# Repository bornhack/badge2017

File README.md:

# Bornhack Badge 2017

## About the hardware

The Bornhack 2017 badge is based around a SiLabs Happy Gecko microcontroller,
an OLED graphical display, a few buttons and a USB interface.

The microcontroller is a Cortex-M0+ with built in USB, specifically we are using
the EFM32HG322F64G and one of the 128x64 pixels OLED displays with an SSD1306
controller.

We have separated the hardware design files from the code and put them in the
[hardware branch][hardware] for you to have a look at and build on.

You can download the microcontroller [reference manual][manual] and
[datasheet][] directly from [SiliconLabs][silabs].

[hardware]: https://github.com/bornhack/badge2017/tree/hardware
[silabs]: https://www.silabs.com/
[manual]: https://www.silabs.com/documents/public/reference-manuals/EFM32HG-RM.pdf
[datasheet]: https://www.silabs.com/documents/public/data-sheets/EFM32HG322.pdf

## About the code

This repo is meant as a starting point for developing your own code
for the Bornhack 2017 badge.

Although *main.c* is quite long it is not meant to scare you. Rather it is
meant to show in all its gory details how to actually program microcontrollers
that doesn't run any operating system without hiding anything behind
a thick API. However to make things readable it does make use of the
[geckonator][] library. This is a very thin wrapper around the registers
of the Happy Gecko chip on the badge. It allows us to write something like
```c
clock_rtc_disable();
```
rather than the more cryptic
```c
CMU->LFACLKEN0 &= ~CMU_LFACLKEN0_RTC;
```
Don't worry. The compiler will sort it out and do exactly as if you'd written the
cryptic version.

Scroll to the bottom of *main.c* and you'll see an infinite loop.
This is the 'mainloop' of the program. It simply waits for events
such as button presses and reacts to those. When there are no
more events to be processed in the internal queue you'll get one last `EVENT_LAST`
event before the chip will sleep and wait for more events.

Events are added to the queue by the interrupt handler functions. You can recognize those
by the fact that they're public (ie. not marked by `static`) and their name will
end in `_IRQHandler`. Before entering the mainloop the chip is configured to
call these handlers on certain events such the voltage on a pin dropping from above 1.5V
to below 0.3V caused by the press of a button.

[geckonator]: https://github.com/flummer/geckonator

## Develop software online

Go to [badge.xil.se](https://badge.xil.se/), click "All Projects" and choose
the official example. Start hacking. Once your code compiles this is how you program
your badge:

1. Click the "Download binary" button to download the compiled code.
2. Connect the USB cable to the board and your computer.
3. Press the **BOOT** button on the badge.
4. Copy the downloaded `.bin`-file to the `GECKOBOOT` USB stick that appeared on your computer.
5. Eject (or unmount) the USB stick, and watch your code run.

## Develop software locally

### 1. Install dependencies

##### Archlinux
```sh
pacman -S arm-none-eabi-gcc arm-none-eabi-newlib make
```

##### Debian/Ubuntu
```sh
apt-get install gcc-arm-none-eabi libnewlib-arm-none-eabi make
```
Unfortunately the toolchain in Ubuntu Trusty 14.04 is too old to work out of the box.

##### Fedora
```sh
dnf install arm-none-eabi-gcc arm-none-eabi-newlib make
```

##### OSX

Download an arm-none-eabi toolchain from ARM [here][arm-toolchain].
Unpack the tarball and update your PATH variable to point to the unpacked `bin` directory.

##### Windows
###### Option 1
Download the apropriate installer from ARM [here][arm-toolchain].
Install it and update your path.
You'll also need GNU Make installed.
A pre-built version can be downloaded [here](http://gnuwin32.sourceforge.net/packages/make.htm).

###### Option 2

Use Windows Subsystem for Linux with Ubuntu 16.04 Xenial or newer and proceed as on Ubuntu above.

### 2. Get the source code

If you already have git installed
```
git clone https://github.com/bornhack/badge2017.git
cd badge2017
```

Otherwise you can download a tarball or zip file from
[https://github.com/bornhack/badge2017](https://github.com/bornhack/badge2017)

### 3. Build the code
Simply type `make` in the downloaded directory.
If the build fails (fx. on Debian Jessie and Ubuntu Xenial)
try editing the `Makefile` and uncommenting the line which says `OLD=1`.

If there are no compilation errors this will result in a `code.bin` in the `out` directory.

[arm-toolchain]: https://developer.arm.com/open-source/gnu-toolchain/gnu-rm/downloads

### 4. Program the badge with your compiled code

###### Option 1

Proceed as above, but instead of downloading your `.bin`-file use the `out/code.bin` you
just generated above.

###### Option 2

Alternatively you can install a program called *dfu-util*. With this program installed
you can simply put the badge in bootloader mode by pressing the **BOOT** button,
and then type `make dfu`. Usually your dfu-util package comes with rules to give
your user (and hence dfu-util) access to the raw USB device. If not you might need
`sudo make dfu`.

## Examples developed during Bornhack 2017

This repo also contains a few branches with examples developed at Barnhack. You can check them out locally with
```sh
git clone -b <BRANCH> https://github.com/bornhack/badge2017.git
```
..or just switch to the branch in your regular clone of this repo.

- [gimp](https://github.com/bornhack/badge2017/tree/gimp) - [gimp](https://www.gimp.org/) can export pictures as C-code usable on the badge
- [bornhackfish](https://github.com/bornhack/badge2017/tree/bornhackfish) - Standard example, but with fish and physics
- [snake](https://github.com/bornhack/badge2017/tree/snake) - Play snake on your badge
- [starfield](https://github.com/bornhack/badge2017/tree/starfield) - Fly through space

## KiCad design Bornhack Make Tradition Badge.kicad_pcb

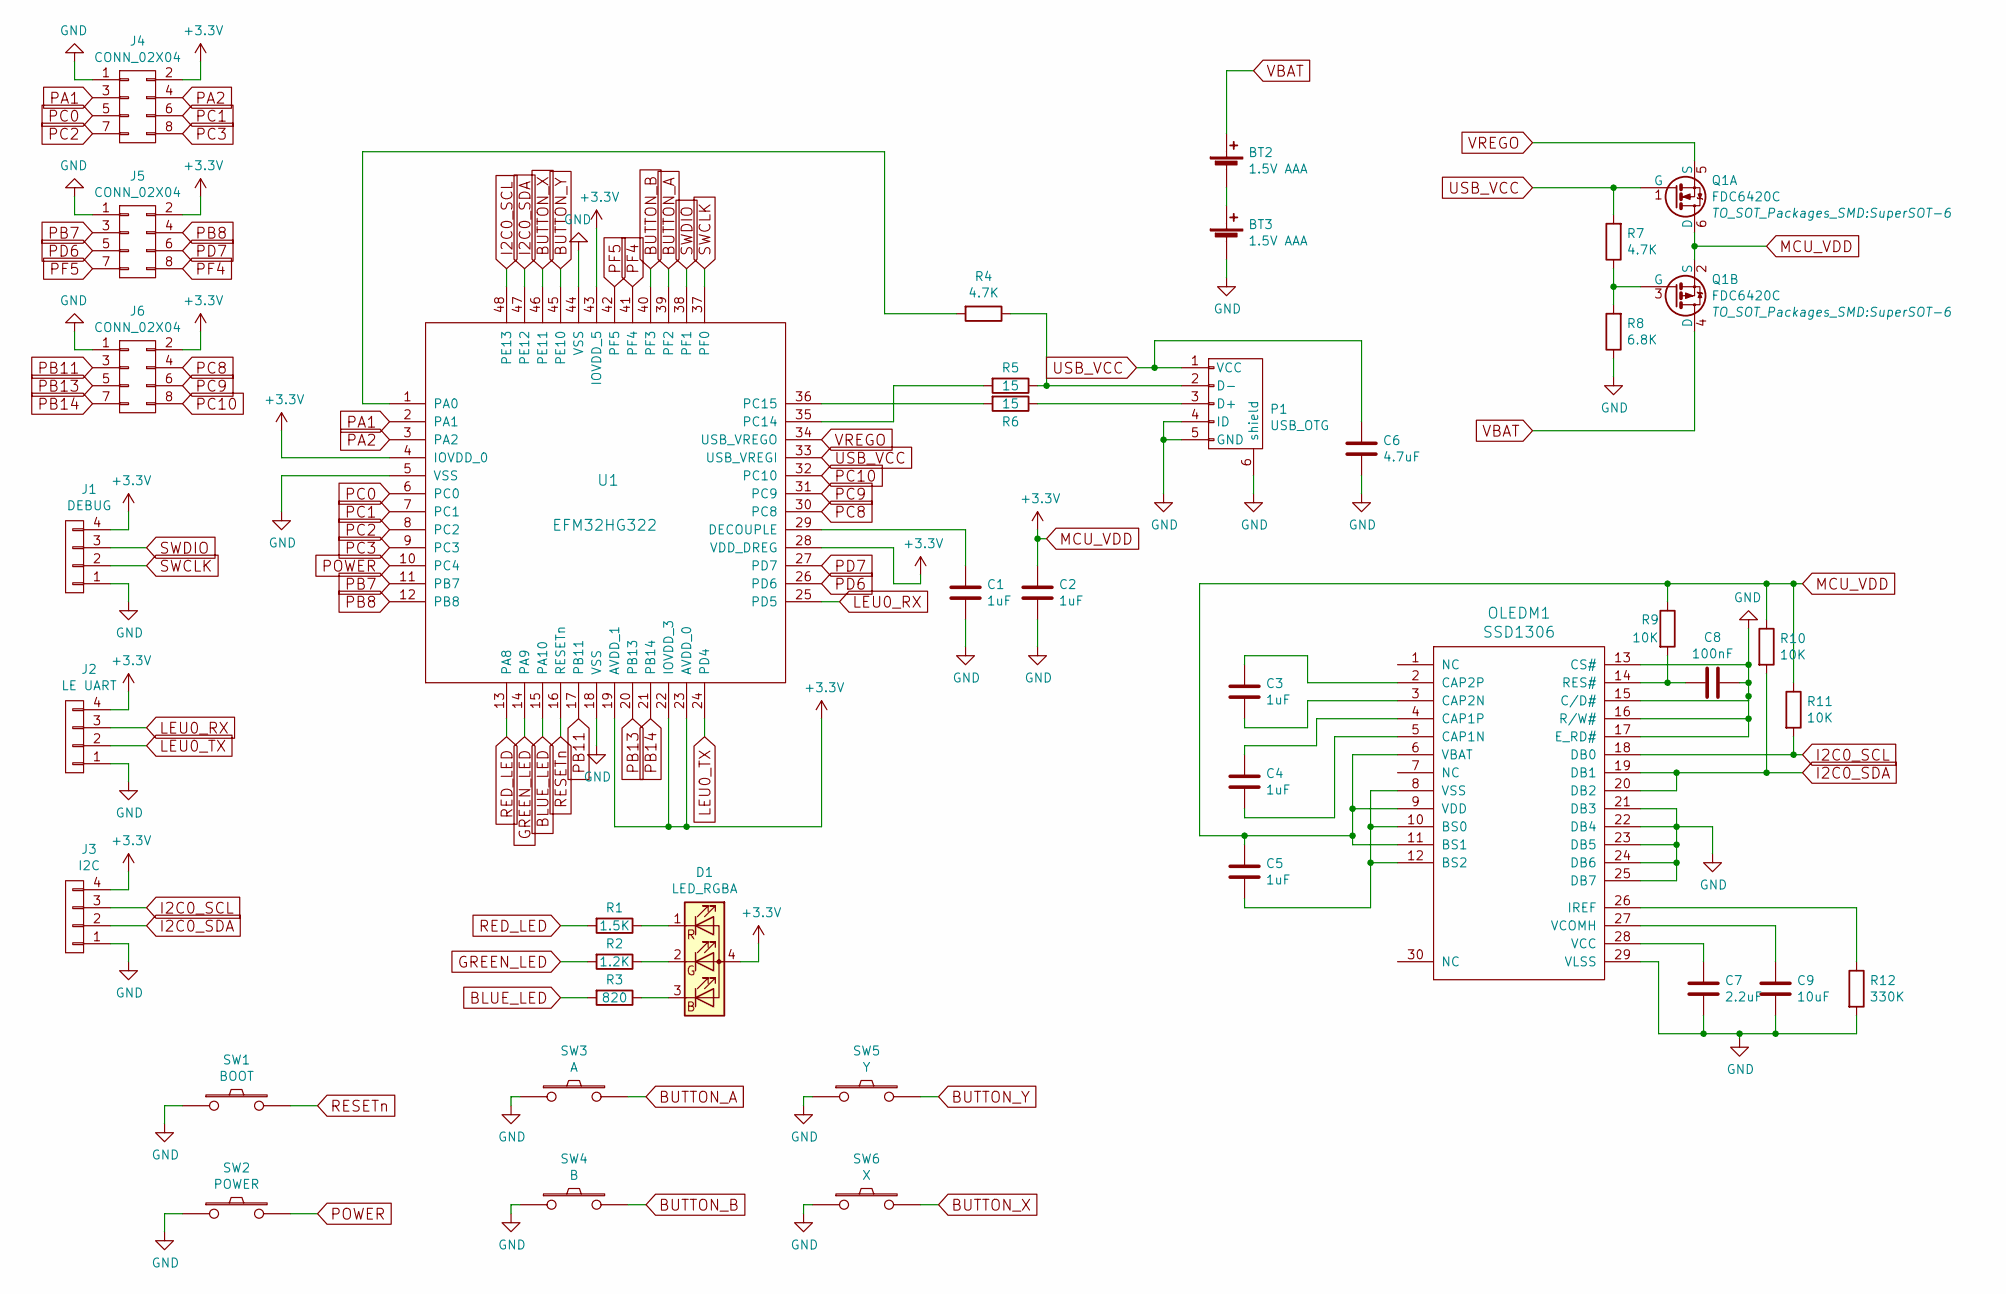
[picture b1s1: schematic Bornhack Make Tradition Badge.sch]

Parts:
BT2, BT3: 1.5V AAA; Keystone_555_AAA_Battery_Clip_pair
C1, C2, C3, C4, C5: 1uF; C_0805
C6: 4.7uF; C_0805
C7: 2.2uF; C_0805
C8: 100nF; C_0805
C9: 10uF; C_0805
D1: LED_RGBA; RGBA_LED_SMD_0606
J1: DEBUG; Pin_Header_Straight_1x04_Pitch2.54mm
J2: LE UART; Pin_Header_Straight_1x04_Pitch2.54mm
J3: I2C; Pin_Header_Straight_1x04_Pitch2.54mm
J4, J5, J6: CONN_02X04; Pin_Header_Straight_2x04_Pitch2.54mm
OLEDM1: SSD1306; IROP055-SSD1306Z
P1: USB_OTG; USB_Micro-B_10103594-0001LF
Q1: FDC6420C; SuperSOT-6
R1: 1.5K; R_0805
R2: 1.2K; R_0805
R3: 820; R_0805
R4, R7: 4.7K; R_0805
R5, R6: 15; R_0805
R8: 6.8K; R_0805
R9, R10, R11: 10K; R_0805
R12: 330K; R_0805
SW1: BOOT; SW_SPST_PTS645
SW2: POWER; SW_SPST_PTS645
SW3: A; SW_SPST_PTS645
SW4: B; SW_SPST_PTS645
SW5: Y; SW_SPST_PTS645
SW6: X; SW_SPST_PTS645
U1: EFM32HG322; TQFP-48_7x7mm_Pitch0.5mm

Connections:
BLUE_LED: R3.2, U1.15 (PA10)
BUTTON_A: SW3.2, U1.39 (PF2)
BUTTON_B: SW4.2, U1.40 (PF3)
BUTTON_X: SW6.2, U1.46 (PE11)
BUTTON_Y: SW5.2, U1.45 (PE10)
GND: BT3.2 (-), C1.2, C2.2, C6.2, C7.2, C8.1, C9.2, J1.1, J2.1, J3.1, J4.1, J5.1, J6.1, OLEDM1.13 (CS#), OLEDM1.15 (C/D#), OLEDM1.16 (R/W#), OLEDM1.17 (E_RD#), OLEDM1.21 (DB3), OLEDM1.22 (DB4), OLEDM1.23 (DB5), OLEDM1.24 (DB6), OLEDM1.25 (DB7), OLEDM1.29 (VLSS), P1.4 (ID), P1.5 (GND), P1.6 (shield), R8.1, R12.2, SW1.1, SW2.1, SW3.1, SW4.1, SW5.1, SW6.1, U1.5 (VSS), U1.18 (VSS), U1.44 (VSS)
GREEN_LED: R2.2, U1.14 (PA9)
I2C0_SCL: J3.3, OLEDM1.18 (DB0), R11.2, U1.48 (PE13)
I2C0_SDA: J3.2, OLEDM1.19 (DB1), OLEDM1.20 (DB2), R10.2, U1.47 (PE12)
LEU0_RX: J2.3, U1.25 (PD5)
LEU0_TX: J2.2, U1.24 (PD4)
MCU_VDD: C2.1, C5.1, D1.4 (A), J1.4, J2.4, J3.4, J4.2, J5.2, J6.2, OLEDM1.6 (VBAT), OLEDM1.9 (VDD), OLEDM1.11 (BS1), Q1.2 (S), Q1.6 (D), R9.1, R10.1, R11.1, U1.4 (IOVDD_0), U1.19 (AVDD_1), U1.22 (IOVDD_3), U1.23 (AVDD_0), U1.28 (VDD_DREG), U1.43 (IOVDD_5)
unnamed: BT2.2 (-), BT3.1 (+)
unnamed: C1.1, U1.29 (DECOUPLE)
unnamed: C3.1, OLEDM1.2 (CAP2P)
unnamed: C3.2, OLEDM1.3 (CAP2N)
unnamed: C4.1, OLEDM1.4 (CAP1P)
unnamed: C4.2, OLEDM1.5 (CAP1N)
unnamed: C5.2, OLEDM1.8 (VSS), OLEDM1.10 (BS0), OLEDM1.12 (BS2)
unnamed: C7.1, OLEDM1.28 (VCC)
unnamed: C8.2, OLEDM1.14 (RES#), R9.2
unnamed: C9.1, OLEDM1.27 (VCOMH)
unnamed: D1.1 (RK), R1.1
unnamed: D1.2 (GK), R2.1
unnamed: D1.3 (BK), R3.1
unnamed: OLEDM1.26 (IREF), R12.1
unnamed: P1.2 (D-), R4.1, R5.1
unnamed: P1.3 (D+), R6.1
unnamed: Q1.3 (G), R7.1, R8.2
unnamed: R4.2, U1.1 (PA0)
unnamed: R5.2, U1.35 (PC14)
unnamed: R6.2, U1.36 (PC15)
PA1: J4.3, U1.2 (PA1)
PA2: J4.4, U1.3 (PA2)
PB7: J5.3, U1.11 (PB7)
PB8: J5.4, U1.12 (PB8)
PB11: J6.3, U1.17 (PB11)
PB13: J6.5, U1.20 (PB13)
PB14: J6.7, U1.21 (PB14)
PC0: J4.5, U1.6 (PC0)
PC1: J4.6, U1.7 (PC1)
PC2: J4.7, U1.8 (PC2)
PC3: J4.8, U1.9 (PC3)
PC8: J6.4, U1.30 (PC8)
PC9: J6.6, U1.31 (PC9)
PC10: J6.8, U1.32 (PC10)
PD6: J5.5, U1.26 (PD6)
PD7: J5.6, U1.27 (PD7)
PF4: J5.8, U1.41 (PF4)
PF5: J5.7, U1.42 (PF5)
POWER: SW2.2, U1.10 (PC4)
RED_LED: R1.2, U1.13 (PA8)
RESETn: SW1.2, U1.16 (RESETn)
SWCLK: J1.2, U1.37 (PF0)
SWDIO: J1.3, U1.38 (PF1)
USB_VCC: C6.1, P1.1 (VCC), Q1.1 (G), R7.2, U1.33 (USB_VREGI)
VBAT: BT2.1 (+), Q1.4 (D)
VREGO: Q1.5 (S), U1.34 (USB_VREGO)

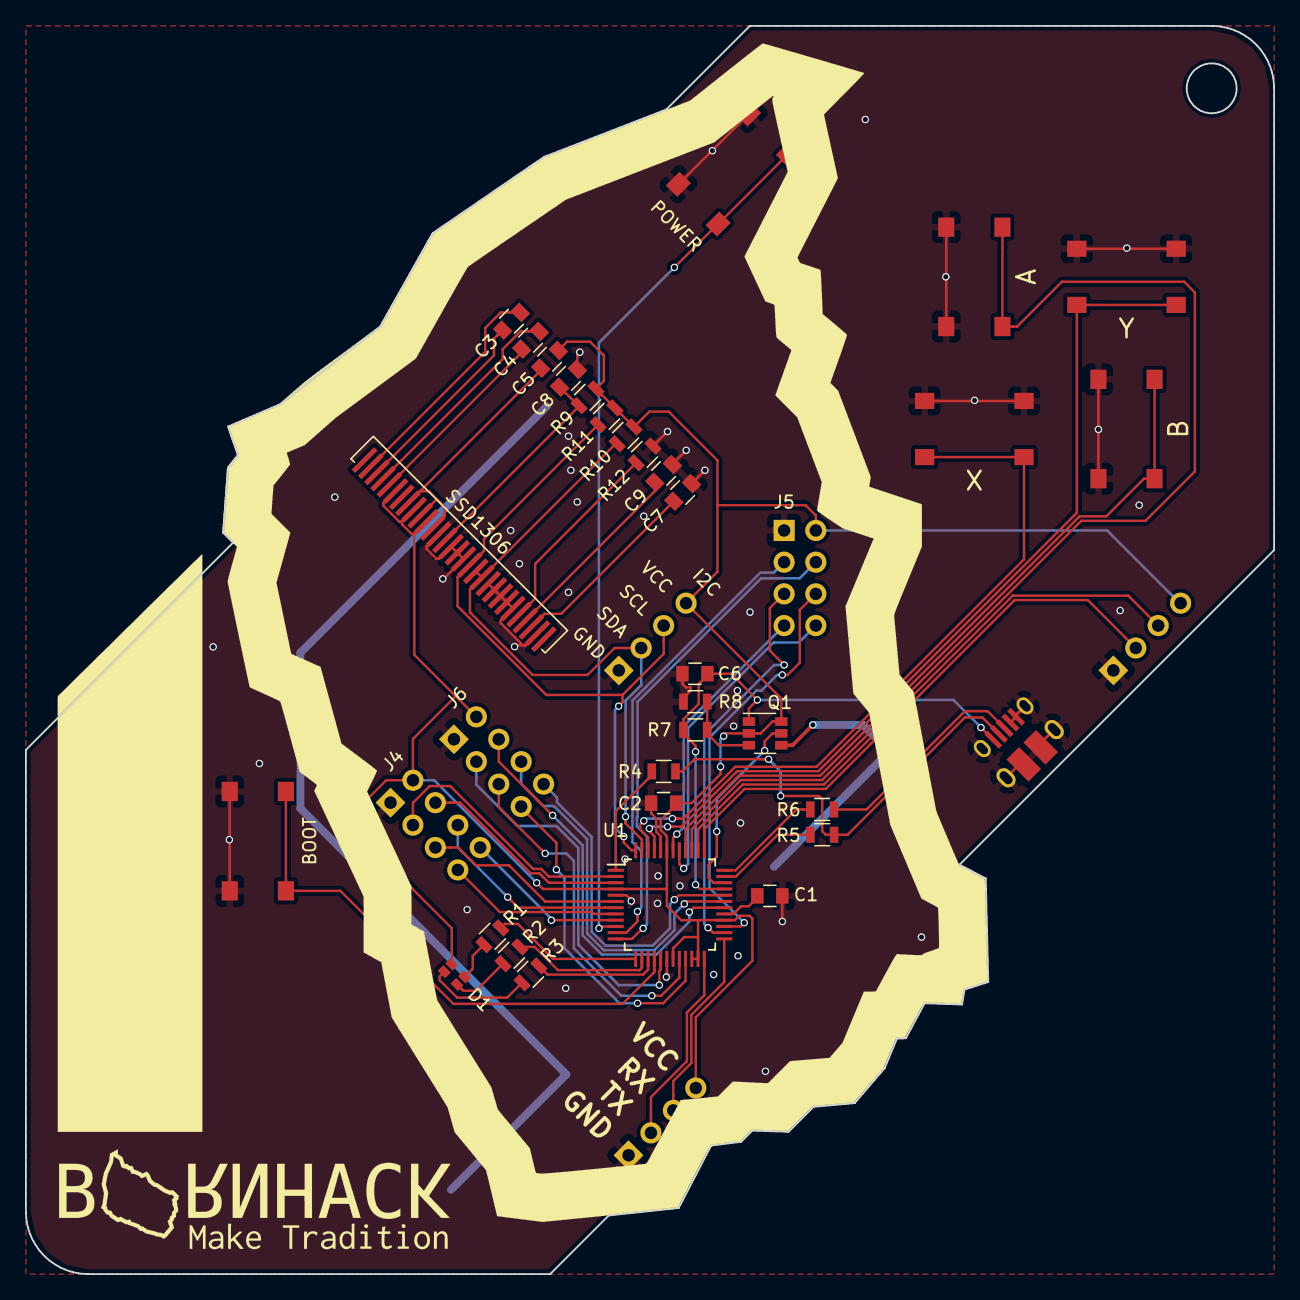
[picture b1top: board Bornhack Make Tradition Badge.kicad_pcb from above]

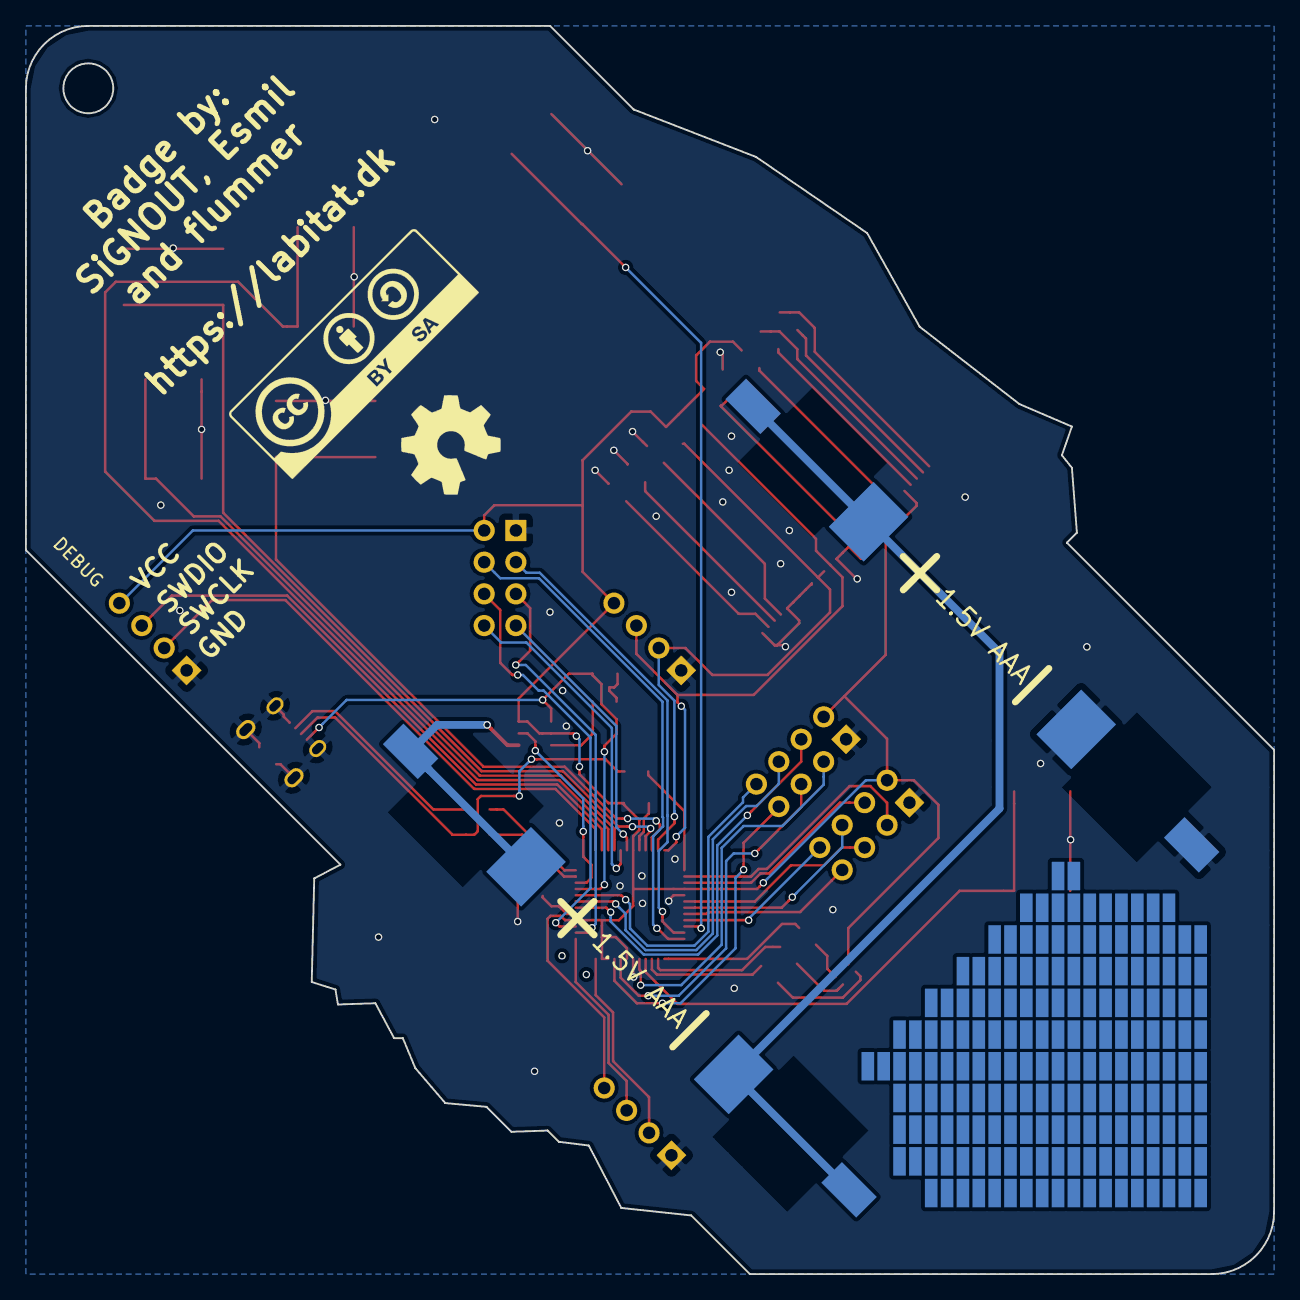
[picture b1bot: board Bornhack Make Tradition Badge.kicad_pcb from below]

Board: 2 copper layers, 100.0 x 100.0 mm, 40 parts (2 on the bottom side), 58 nets.

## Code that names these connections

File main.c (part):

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}

static struct button buttons[] = {
	{ .n.fn = button_callback, .pin = GPIO_PF2,  .event = EVENT_BUTTON_A_DOWN,
		.delay = 350, .repeat = 80 },
	{ .n.fn = button_callback, .pin = GPIO_PF3,  .event = EVENT_BUTTON_B_DOWN,
		.delay = 350, .repeat = 80 },
	{ .n.fn = button_callback, .pin = GPIO_PE11, .event = EVENT_BUTTON_X_DOWN,
		.delay = 350, .repeat = 80 },
	{ .n.fn = button_callback, .pin = GPIO_PE10, .event = EVENT_BUTTON_Y_DOWN,
		.delay = 350, .repeat = 80 },
	{ .n.fn = button_callback, .pin = GPIO_PC4,  .event = EVENT_BUTTON_POWER_DOWN,
		.delay = 50, .repeat = 0 },
};

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{
	unsigned int flags = gpio_flags_enabled(gpio_flags());

	if (gpio_flag(flags, GPIO_PF2))
		button_firstclick(&buttons[0]);
	if (gpio_flag(flags, GPIO_PE10))
		button_firstclick(&buttons[3]);
	if (gpio_flag(flags, GPIO_PC4))
		button_firstclick(&buttons[4]);
}

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{
	unsigned int flags = gpio_flags_enabled(gpio_flags());

	if (gpio_flag(flags, GPIO_PF3))
		button_firstclick(&buttons[1]);
	if (gpio_flag(flags, GPIO_PE11))
		button_firstclick(&buttons[2]);
}

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	clock_peripheral_div1();
	clock_i2c0_enable();
	i2c0_clock_div(3); /* Thigh = Tlow = (4*(3 + 1) + 4) / (14MHz) = 1.43 us */
	i2c0_pins(I2C_PINS_ENABLE6); /* SDA -> PE12, SCL -> PE13 */
	i2c0_config(I2C_CONFIG_ENABLE);
	i2c0_abort(); /* we're the only master, so start transmitting immediately */
	i2c0_flags_enable(I2C_FLAG_NACK | I2C_FLAG_MSTOP);
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	uint8_t state;
	uint8_t mode;
} gpio_pins[] = {
	{ GPIO_PA8,  1, GPIO_MODE_WIREDAND }, /* red   LED */
	{ GPIO_PA9,  1, GPIO_MODE_WIREDAND }, /* green LED */
	{ GPIO_PA10, 1, GPIO_MODE_WIREDAND }, /* blue  LED */
	{ GPIO_PC4,  1, GPIO_MODE_INPUTPULLFILTER }, /* POWER button */
	{ GPIO_PE10, 1, GPIO_MODE_INPUTPULLFILTER }, /* Y button */
	{ GPIO_PE11, 1, GPIO_MODE_INPUTPULLFILTER }, /* X button */
	{ GPIO_PE12, 1, GPIO_MODE_WIREDAND }, /* I2C0 SDA */
	{ GPIO_PE13, 1, GPIO_MODE_WIREDAND }, /* I2C0 SCL */
	{ GPIO_PF2,  1, GPIO_MODE_INPUTPULLFILTER }, /* A button */
	{ GPIO_PF3,  1, GPIO_MODE_INPUTPULLFILTER }, /* B button */
};

static void
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	for (i = 0; i < ARRAY_SIZE(gpio_pins); i++) {
		gpio_pin_t pin = gpio_pins[i].pin;

		if (gpio_pin_eq(pin, GPIO_PC4))
			continue;

		gpio_mode(pin, GPIO_MODE_DISABLED);
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	gpio_retention_enable();
	/* wake up when pin goes low */
	gpio_wakeup_rising(0);
	/* enable EM4 wake-up from PC4 */
	gpio_wakeup_pins(GPIO_WAKEUP_PC4);

	/* do the EM4 handshake */
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	rgb_enabled = true;

	/* make sure the POWER button is released */
	while (!gpio_in(GPIO_PC4))
		msleep(50);
	msleep(10);

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
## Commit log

2017-07-24 First developer revision
    The first version that was manufactured for testing
2017-07-30 Flipped D+ and D- and removed dual battery option
    - D+ and D- has been corrected
    - Coin cell holder has been removed, since the badge uses too much power when the screen is on for a coin cell to be a reasonable power source.
    - Current measurement pin headers have also been removed.
2017-07-30 Changed pins for 2 buttons, cleanup and proto pads
    - Changed the pins for the LEFT (X) and RIGHT (Y) buttons so that all buttons have their own interrupt
    - Changed the name of the buttons to A, B, X and Y so that the names also make sense, when the badge is oriented differently
    - Removed silkscreen lines around buttons and non populated pin headers
    - Added SMD prototyping area on the back
    - Added Open Hardware Logo and CC-BY-SA graphics
    - Updated gerber files (production run)
2017-08-14 Updated description
2017-08-14 Added license and readme
2017-08-15 README: try to prevent github from mangling URL
2017-08-15 README: "gory details" is the correct phrase
2017-08-16 Fix X, Y button pin comments
2017-08-17 README: add microcontroller manual and datasheet links
2017-08-17 README: bootloader now accepts any .bin file
2017-08-18 README: fix Debian/Ubuntu gcc package name
    Thanks, kokanin!
2017-08-18 Make i2c handling a little more robust
2017-08-19 Better-feeling buttons
2017-08-20 Remove i2c0_write macro sillyness
2017-08-21 Add more comments and small cleanups
2017-08-21 Show the Bornhack 2017 schedule on the display
2017-08-22 README: add badge.xil.se link
2017-08-23 Add ticker code to get periodic events
2017-08-23 README: explain about dfu-util
2017-08-23 geckonator: update to target specific dfu device
2017-08-24 Init snake
2017-08-24 render bornhack logo
2017-08-24 add second image
2017-08-25 hungry fish
2017-08-25 Add display.c
    - It contains some of the display_ functions that I may like to use in other places as well.
2017-08-25 enable rendering of frames
2017-08-25 Add xcf files
2017-08-27 Add serial output example code
2017-08-28 Starfield animation + RGB animation + flashlight option when pressing Y.
2017-09-03 scalable fishes
    forked original so the up key now rounds and the down key has new
    images. the third one is with fishes. for this there is a fish function
    that is able to print fishes left- or rightfaced onto the screen with
    variable sizes
2017-09-03 fish can swim
    random fishes swim. main problem was modulo and unsigned ints
2017-09-03 doublependulum
    - velocity increases but renders slower
    - differential equation problems
    - no influence of one weight onto the other
2017-09-03 Now energy preserving
    - the problem was, I turned the old acceleration vector, but it has to
    be projected. Then the velocity is scaled for energy preserving with
    sqrt(2(h_0-h)g)
    - the weights are still not influencing each other
2017-09-03 The two weights try to influence each other
    - If the velocity of the one directs away of the string to the other, it
    pulls
    - maybe contains still bugs
2017-09-05 README: add references to example branches
2017-09-10 Make use of the DMA controller when using the I2C bus for better power friendliness
2018-08-04 ics: ignore long descriptions
2018-08-04 ics: update to 2018

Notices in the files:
main.c:
Copyright 2017 Emil Renner Berthing <esmil@labitat.dk>
modify it under the terms of the GNU General Public License as published
